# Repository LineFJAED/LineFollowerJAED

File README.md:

# LineFollowerJAED
Proyecto de código abierto, seguidor de línea, y proyecto de módulo.

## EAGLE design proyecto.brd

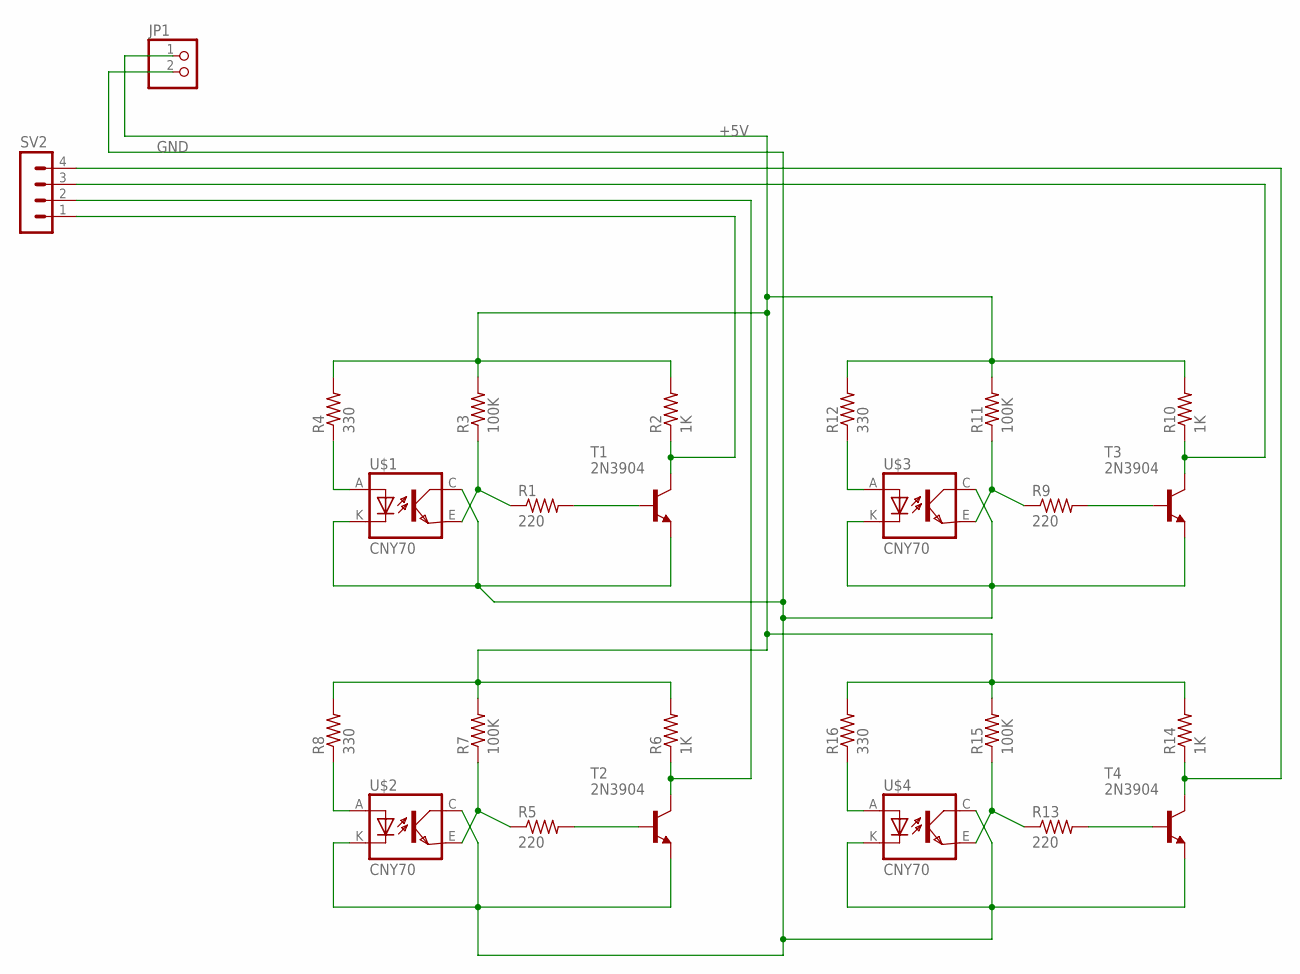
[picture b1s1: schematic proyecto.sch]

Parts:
JP1: PINHD-1X2; 1X02
R1, R5, R9, R13: 220; 0207/10
R2, R6, R10, R14: 1K; 0207/10
R3, R7, R11, R15: 100K; 0207/10
R4, R8, R12, R16: 330; 0207/10
SV2: MA04-1
T1, T2, T3, T4: 2N3904; TO92
U$1, U$2, U$3, U$4: CNY70; 4

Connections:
+5V: JP1.1, R2.2, R3.2, R4.2, R6.2, R7.2, R8.2, R10.2, R11.2, R12.2, R14.2, R15.2, R16.2
GND: JP1.2, T1.3 (E), T2.3 (E), T3.3 (E), T4.3 (E), U$1.C (COL), U$1.K (C), U$2.C (COL), U$2.K (C), U$3.C (COL), U$3.K (C), U$4.C (COL), U$4.K (C)
unnamed: R1.1, R3.1, U$1.E (EMI)
unnamed: R4.1, U$1.A
unnamed: R5.1, R7.1, U$2.E (EMI)
unnamed: R8.1, U$2.A
unnamed: R1.2, T1.2 (B)
unnamed: R5.2, T2.2 (B)
unnamed: R9.1, R11.1, U$3.E (EMI)
unnamed: R12.1, U$3.A
unnamed: R9.2, T3.2 (B)
unnamed: R13.1, R15.1, U$4.E (EMI)
unnamed: R16.1, U$4.A
unnamed: R13.2, T4.2 (B)
S1: R2.1, SV2.1, T1.1 (C)
S2: R6.1, SV2.2, T2.1 (C)
S3: R10.1, SV2.3, T3.1 (C)
S4: R14.1, SV2.4, T4.1 (C)

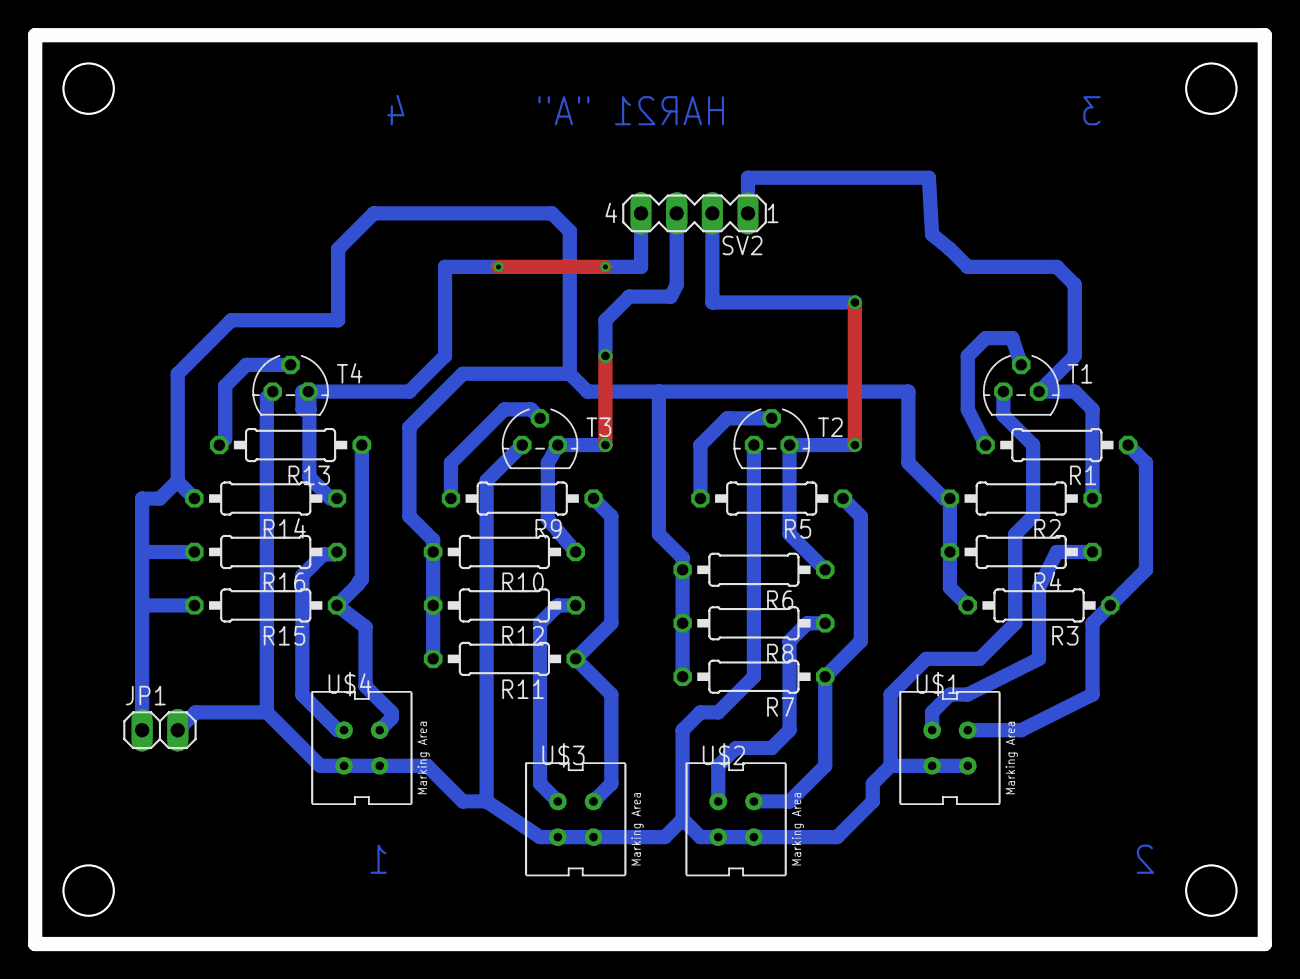
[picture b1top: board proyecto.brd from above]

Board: 2 copper layers, 87.6 x 64.8 mm, 26 parts (0 on the bottom side), 18 nets.

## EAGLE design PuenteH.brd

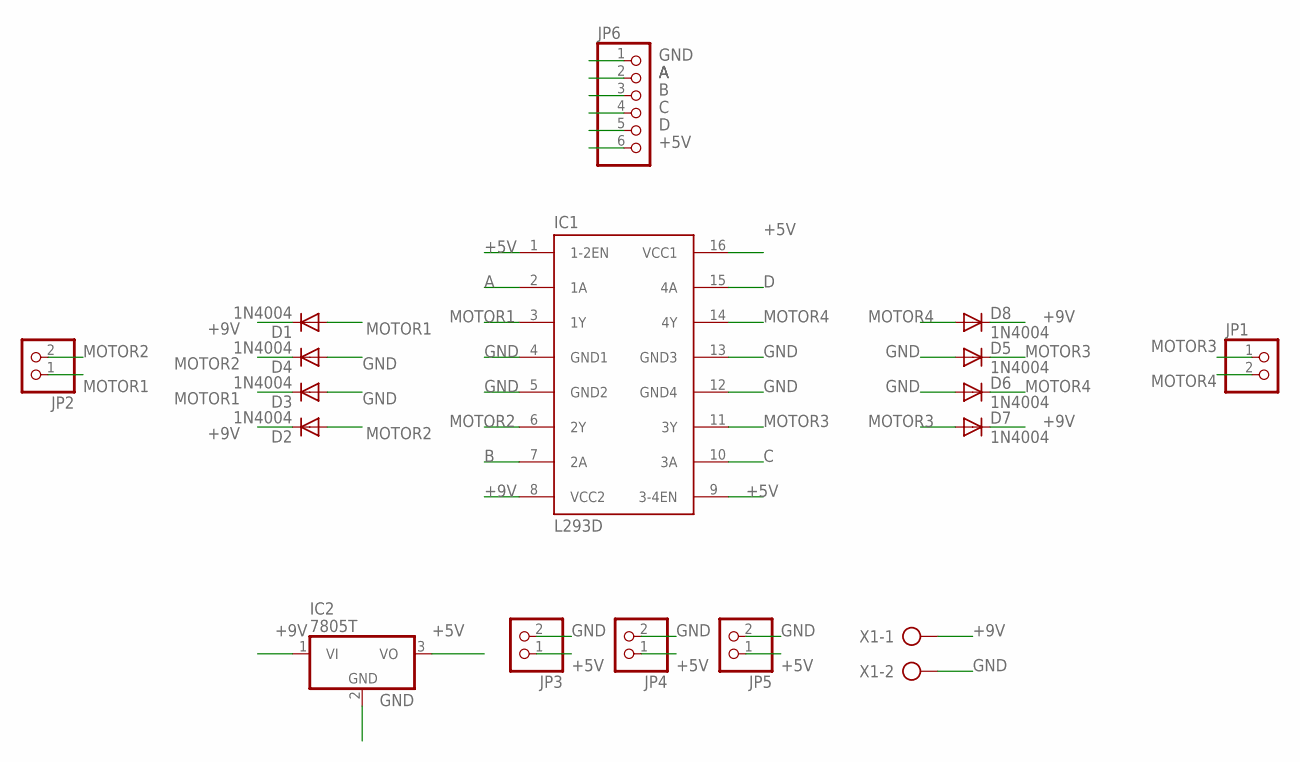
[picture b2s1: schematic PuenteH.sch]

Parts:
D1, D2, D3, D4, D5, D6, D7, D8: 1N4004; DO41-10
IC1: L293D; DIL16
IC2: 7805T; TO220H
JP1, JP2, JP3, JP4, JP5: PINHD-1X2; 1X02
JP6: PINHD-1X6; 1X06
X1: AK500/2-H

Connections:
+5V: IC1.1 (1-2EN), IC1.9 (3-4EN), IC1.16 (VCC1), IC2.3 (VO), JP3.1, JP4.1, JP5.1, JP6.6
+9V: D1.C, D2.C, D7.C, D8.C, IC1.8 (VCC2), IC2.1 (VI), X1.1
A: IC1.2 (1A), JP6.2
B: IC1.7 (2A), JP6.3
C: IC1.10 (3A), JP6.4
D: IC1.15 (4A), JP6.5
GND: D3.A, D4.A, D5.A, D6.A, IC1.4 (GND1), IC1.5 (GND2), IC1.12 (GND4), IC1.13 (GND3), IC2.2 (GND), JP3.2, JP4.2, JP5.2, JP6.1, X1.2
MOTOR1: D1.A, D3.C, IC1.3 (1Y), JP2.1
MOTOR2: D2.A, D4.C, IC1.6 (2Y), JP2.2
MOTOR3: D5.C, D7.A, IC1.11 (3Y), JP1.1
MOTOR4: D6.C, D8.A, IC1.14 (4Y), JP1.2

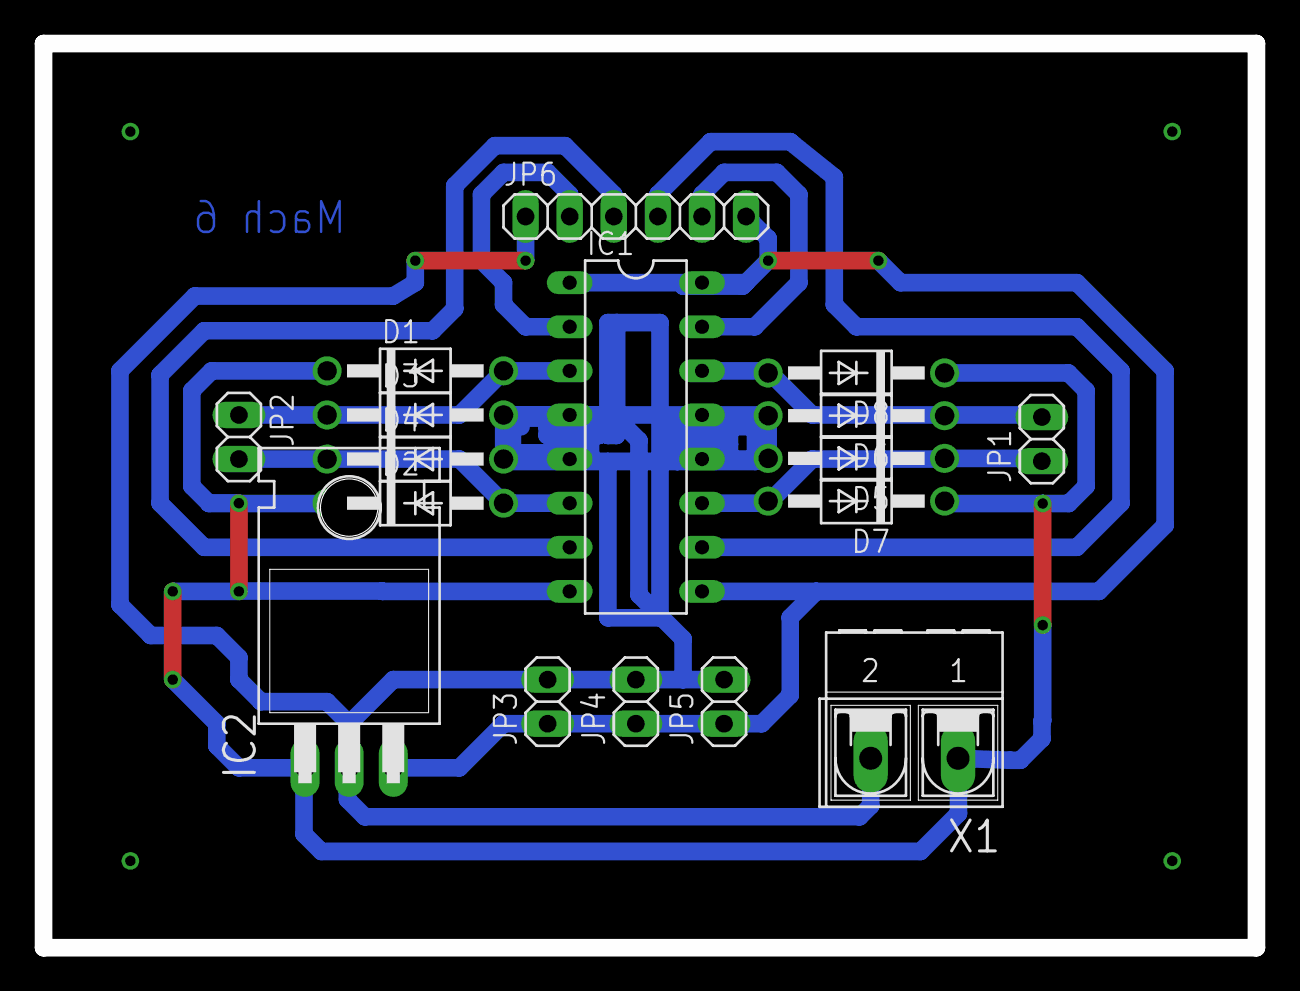
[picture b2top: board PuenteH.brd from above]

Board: 2 copper layers, 69.8 x 52.1 mm, 17 parts (0 on the bottom side), 11 nets.

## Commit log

2018-05-24 Puente H
    Driver para motores a utilizar en el proyecto
2018-05-24 Módulo CNY70
    Sensor de luz del seguidor de linea
2018-05-24 Cambio 1 Puente
    Adición de agujeros
2018-05-24 Primer cambio en sensores
2018-05-24 Update con pdf´s
2018-06-07 Codigo del proyecto
    Lenguaje de programación: Python
    Placa de desarrollo: Raspberry Pi 3 B+
2018-06-13 Ultimos cambios del seguidor de linea
    Se agregan el diseño del chasis, el código final se modifica y se agrega en paper del seguidor de linea
